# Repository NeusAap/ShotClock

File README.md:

# ShotClock hardware & software
This project entails the creation of a poker shot clock. The device is designed to manage the timing of player decisions during a poker game, enhancing the pace of play and ensuring fair timing for all participants. 

# Folder structure
1. `doc`: Contains design documents & notes/questions
2. `hw/ShotClockProject`: Contains KiCAD 7.0.6 design files for hardware
3. `hw/ShotClockProject/output`: Contains hardware output files (plots, PDFs etc.)
4. `sw`: contains STM32CubeIDE firmware

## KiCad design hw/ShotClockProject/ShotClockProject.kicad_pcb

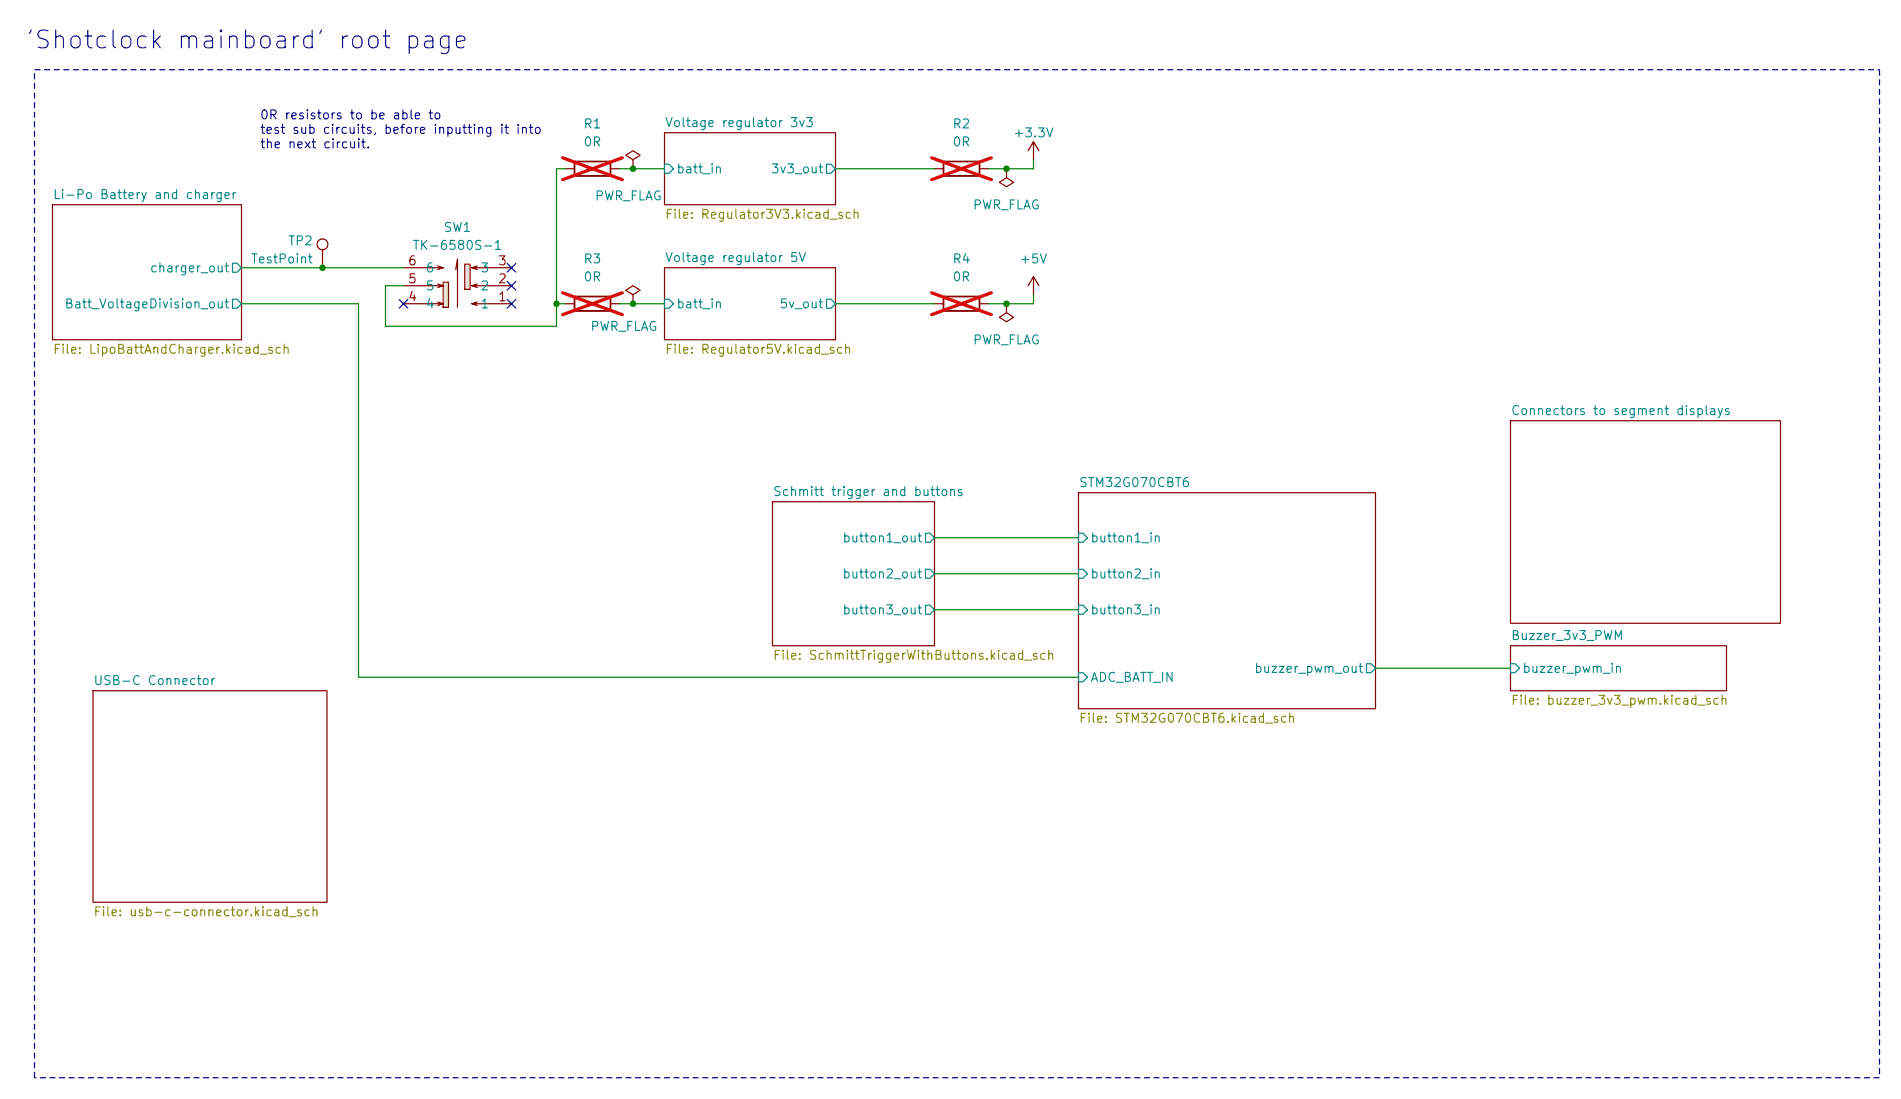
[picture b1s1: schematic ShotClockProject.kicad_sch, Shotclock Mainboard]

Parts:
R1, R2, R3, R4: 0R; R_0402_1005Metric; LCSC Part C17168; not fitted
SW1: TK-6580S-1; SW-SMD_TK-6580S-1; LCSC Part C528774
TP2: TestPoint; TestPoint_Pad_D1.0mm

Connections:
+3.3V: R2.2; also elsewhere on the board
+5V: R4.2; also elsewhere on the board
/Li-Po Battery and charger/charger_out: SW1.6, TP2.1; also elsewhere on the board
/Voltage regulator 3v3/3v3_out: R2.1; also elsewhere on the board
/Voltage regulator 3v3/batt_in: R1.2; also elsewhere on the board
/Voltage regulator 5V/5v_out: R4.1; also elsewhere on the board
/Voltage regulator 5V/batt_in: R3.2; also elsewhere on the board
unnamed: R1.1, R3.1, SW1.5

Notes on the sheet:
0R resistors to be able to test sub circuits, before inputting it into the next circuit.
'Shotclock mainboard' root page

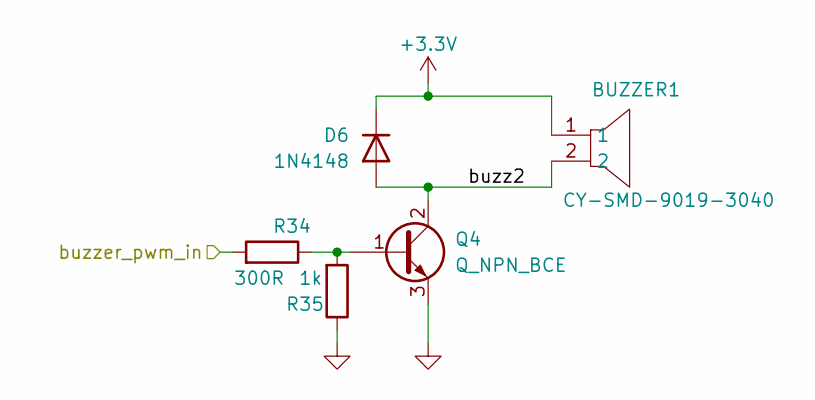
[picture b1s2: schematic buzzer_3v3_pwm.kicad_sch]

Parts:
BUZZER1: CY-SMD-9019-3040; BUZ-SMD_L9.0-W9.0-P8.00-LS9.3_CY; JLC Part Extended Part
D6: 1N4148; D_SOD-323; LCSC Part C2128
Q4: Q_NPN_BCE; SOT-23; LCSC Part C111113
R34: 300R; R_0402_1005Metric; LCSC Part C25102
R35: 1k; R_0402_1005Metric; LCSC Part C105637

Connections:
+3.3V: BUZZER1.1, D6.1 (K); also elsewhere on the board
/Buzzer_3v3_PWM/buzz2: BUZZER1.2, D6.2 (A), Q4.2 (C)
/Buzzer_3v3_PWM/buzzer_pwm_in: R34.2; also elsewhere on the board
GND: Q4.3 (E), R35.1; also elsewhere on the board
unnamed: Q4.1 (B), R34.1, R35.2

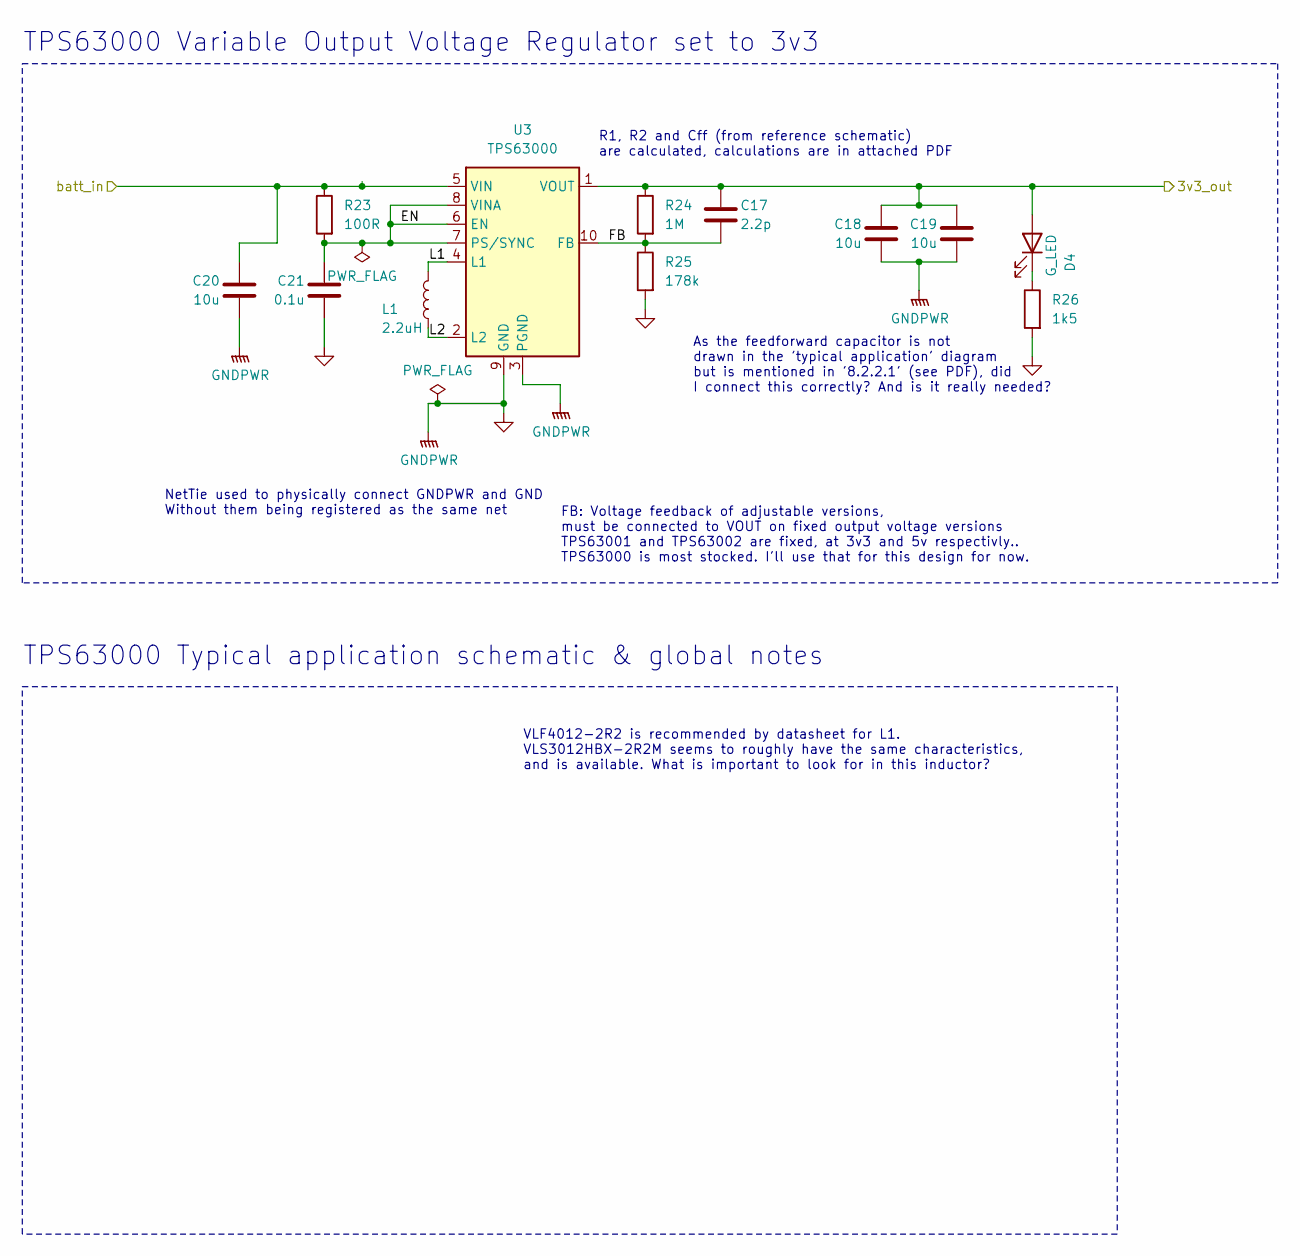
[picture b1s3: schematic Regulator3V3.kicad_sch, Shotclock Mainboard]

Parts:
C17: 2.2p; C_0402_1005Metric; LCSC Part C1559
C18, C19, C20: 10u; C_0603_1608Metric; LCSC Part C96446
C21: 0.1u; C_0402_1005Metric; LCSC Part C1525
D4: G_LED; LED_0603_1608Metric; LCSC Part C72043
L1: 2.2uH; L_Sunlord_SWPA3012S; LCSC Part C404494
R23: 100R; R_0402_1005Metric; LCSC Part C25076
R24: 1M; R_0402_1005Metric; LCSC Part C144787
R25: 178k; R_0402_1005Metric; LCSC Part C185459
R26: 1k5; R_0402_1005Metric; LCSC Part C25867
U3: TPS63000; Texas_DRC0010J_Altered; LCSC Part C24966

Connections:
/Voltage regulator 3v3/3v3_out: C17.1, C18.1, C19.1, D4.2 (A), R24.1, U3.1 (VOUT); also elsewhere on the board
/Voltage regulator 3v3/EN: C21.1, R23.2, U3.6 (EN), U3.7 (PS/SYNC), U3.8 (VINA)
/Voltage regulator 3v3/FB: C17.2, R24.2, R25.1, U3.10 (FB)
/Voltage regulator 3v3/L1: L1.1, U3.4 (L1)
/Voltage regulator 3v3/L2: L1.2, U3.2 (L2)
/Voltage regulator 3v3/batt_in: C20.1, R23.1, U3.5 (VIN); also elsewhere on the board
GND: C18.2, C19.2, C20.2, C21.2, R25.2, R26.2, U3.3 (PGND), U3.9 (GND), U3.11 (PGND); also elsewhere on the board
unnamed: D4.1 (K), R26.1

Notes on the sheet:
As the feedforward capacitor is not drawn in the 'typical application' diagram but is mentioned in '8.2.2.1' (see PDF), did I connect this correctly? And is it really needed?
NetTie used to physically connect GNDPWR and GND Without them being registered as the same net
R1, R2 and Cff (from reference schematic) are calculated, calculations are in attached PDF
FB: Voltage feedback of adjustable versions, must be connected to VOUT on fixed output voltage versions TPS63001 and TPS63002 are fixed, at 3v3 and 5v respectivly.. TPS63000 is most stocked. I'll use that for this design for now.
TPS63000 Variable Output Voltage Regulator set to 3v3
VLF4012-2R2 is recommended by datasheet for L1. VLS3012HBX-2R2M seems to roughly have the same characteristics, and is available. What is important to look for in this inductor?
TPS63000 Typical application schematic & global notes

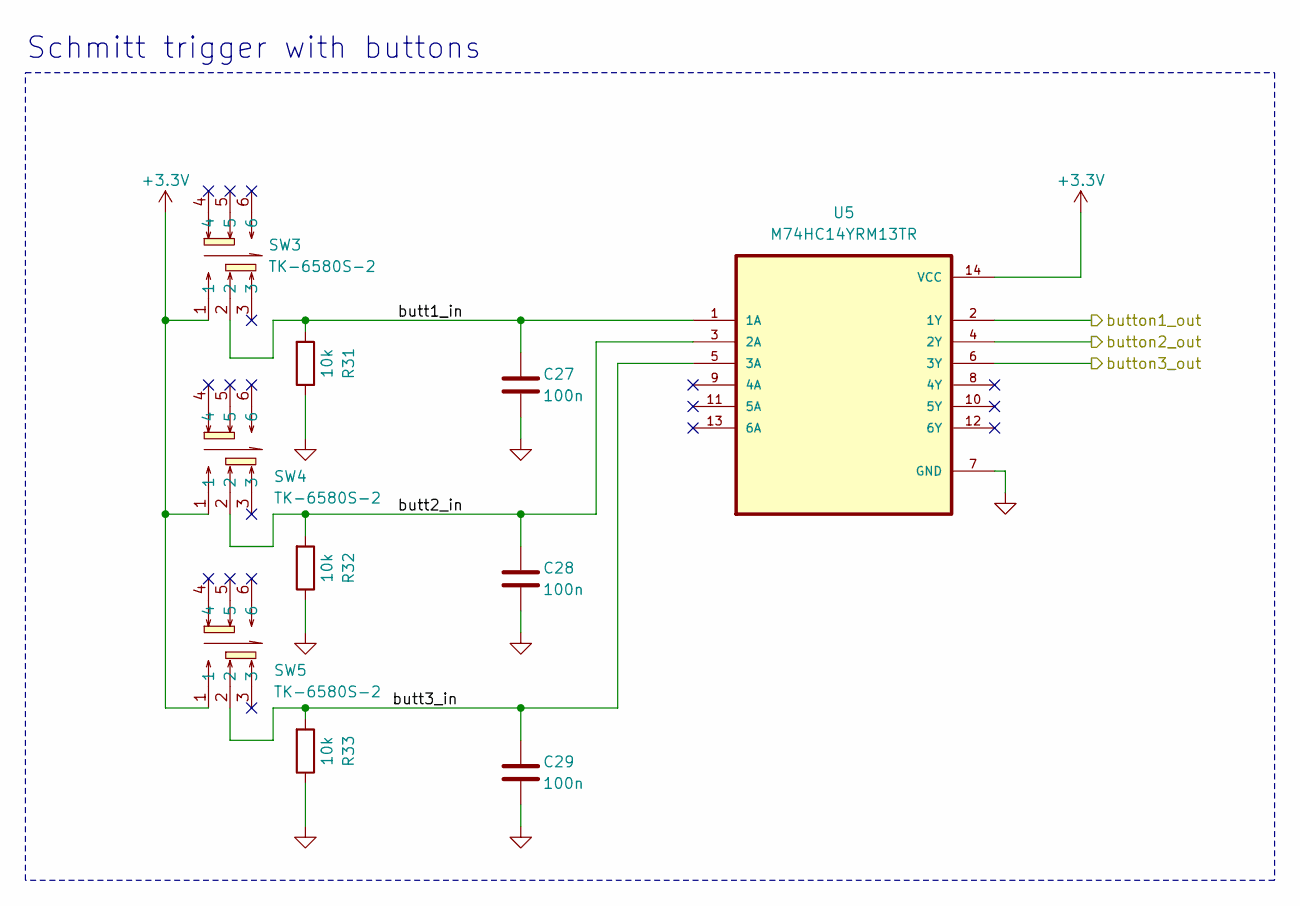
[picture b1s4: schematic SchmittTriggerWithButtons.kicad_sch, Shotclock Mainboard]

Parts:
C27, C28, C29: 100n; C_0402_1005Metric; LCSC Part C1525
R31, R32, R33: 10k; R_0402_1005Metric; LCSC Part C25744
SW3, SW4, SW5: TK-6580S-2; SW-SMD_TK-6580S-2; LCSC Part C528775
U5: M74HC14YRM13TR; SOIC-14_3.9x8.7mm_P1.27mm; LCSC Part C157450

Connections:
+3.3V: SW3.1, SW4.1, SW5.1, U5.14 (VCC); also elsewhere on the board
/STM32G070CBT6/button1_in: U5.2 (1Y); also elsewhere on the board
/STM32G070CBT6/button2_in: U5.4 (2Y); also elsewhere on the board
/STM32G070CBT6/button3_in: U5.6 (3Y); also elsewhere on the board
/Schmitt trigger and buttons/butt1_in: C27.1, R31.2, SW3.2, U5.1 (1A)
/Schmitt trigger and buttons/butt2_in: C28.1, R32.2, SW4.2, U5.3 (2A)
/Schmitt trigger and buttons/butt3_in: C29.1, R33.2, SW5.2, U5.5 (3A)
GND: C27.2, C28.2, C29.2, R31.1, R32.1, R33.1, U5.7 (GND); also elsewhere on the board

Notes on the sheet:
Schmitt trigger with buttons

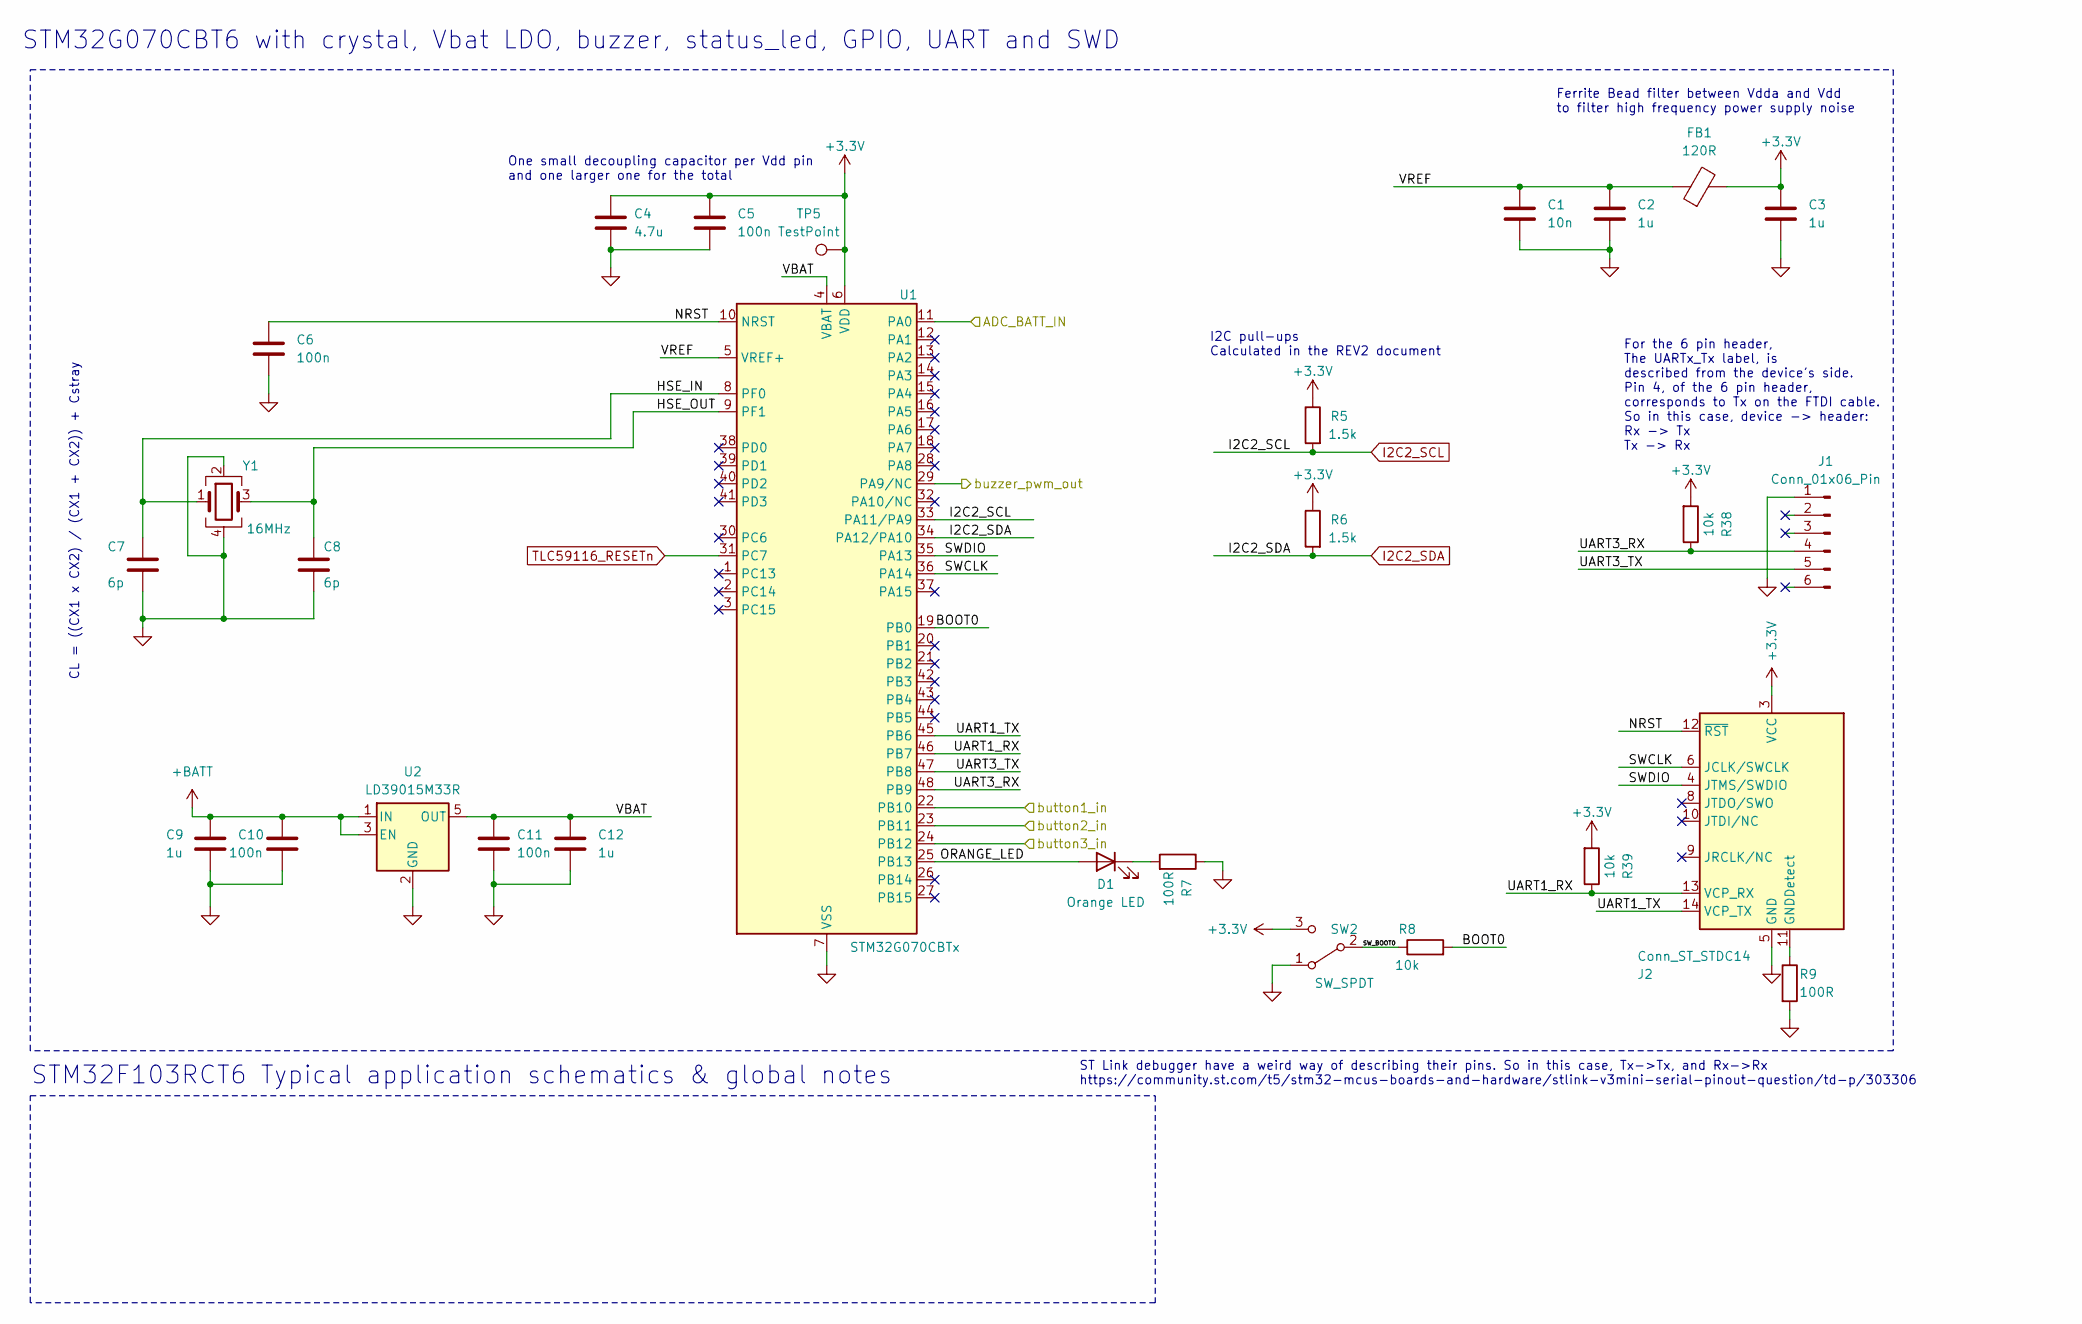
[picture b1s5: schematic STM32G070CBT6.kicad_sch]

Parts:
C1: 10n; C_0402_1005Metric; LCSC Part C15195
C2, C3, C9, C12: 1u; C_0402_1005Metric; LCSC Part C52923
C4: 4.7u; C_0402_1005Metric; LCSC Part C23733
C5, C6, C10, C11: 100n; C_0402_1005Metric; LCSC Part C1525
C7, C8: 6p; C_0402_1005Metric; LCSC Part C1575
D1: Orange LED; LED_0603_1608Metric; LCSC Part C264451
FB1: 120R; L_0603_1608Metric; LCSC Part C127301
J1: Conn_01x06_Pin; PinHeader_1x06_P2.54mm_Horizontal; LCSC Part C56816
J2: Conn_ST_STDC14; PinHeader_2x07_P1.27mm_Vertical_SMD; LCSC Part C3975190
R5, R6: 1.5k; R_0402_1005Metric; LCSC Part C25867
R7, R9: 100R; R_0402_1005Metric; LCSC Part C25076
R8, R38, R39: 10k; R_0402_1005Metric; LCSC Part C25744
SW2: SW_SPDT; SW_SPDT_PCM12_Upwards; LCSC Part C500057
TP5: TestPoint; TestPoint_Pad_D1.0mm
U1: STM32G070CBTx; LQFP-48_7x7mm_P0.5mm; LCSC Part C529338
U2: LD39015M33R; SOT-23-5; LCSC Part C2798212
Y1: 16MHz; Crystal_SMD_3225-4Pin_3.2x2.5mm; LCSC Part C112972

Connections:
+3.3V: C3.1, C4.1, C5.1, FB1.2, J2.3 (VCC), R5.1, R6.1, R38.2, R39.2, SW2.3 (C), TP5.1, U1.6 (VDD); also elsewhere on the board
+BATT: C9.1, C10.1, U2.1 (IN), U2.3 (EN); also elsewhere on the board
/Buzzer_3v3_PWM/buzzer_pwm_in: U1.29 (PA9/NC); also elsewhere on the board
/Li-Po Battery and charger/Batt_VoltageDivision_out: U1.11 (PA0); also elsewhere on the board
/STM32G070CBT6/BOOT0: R8.2, U1.19 (PB0)
/STM32G070CBT6/HSE_IN: C7.1, U1.8 (PF0), Y1.1
/STM32G070CBT6/HSE_OUT: C8.1, U1.9 (PF1), Y1.3
/STM32G070CBT6/NRST: C6.1, J2.12 (~RST), U1.10 (NRST)
/STM32G070CBT6/ORANGE_LED: D1.2 (A), U1.25 (PB13)
/STM32G070CBT6/SWCLK: J2.6 (JCLK/SWCLK), U1.36 (PA14)
/STM32G070CBT6/SWDIO: J2.4 (JTMS/SWDIO), U1.35 (PA13)
/STM32G070CBT6/SW_BOOT0: R8.1, SW2.2 (B)
/STM32G070CBT6/UART1_RX: J2.13 (VCP_RX), R39.1, U1.46 (PB7)
/STM32G070CBT6/UART1_TX: J2.14 (VCP_TX), U1.45 (PB6)
/STM32G070CBT6/UART3_RX: J1.4, R38.1, U1.48 (PB9)
/STM32G070CBT6/UART3_TX: J1.5, U1.47 (PB8)
/STM32G070CBT6/VBAT: C11.1, C12.1, U1.4 (VBAT), U2.5 (OUT)
/STM32G070CBT6/VREF: C1.1, C2.1, FB1.1, U1.5 (VREF+)
/STM32G070CBT6/button1_in: U1.22 (PB10); also elsewhere on the board
/STM32G070CBT6/button2_in: U1.23 (PB11); also elsewhere on the board
/STM32G070CBT6/button3_in: U1.24 (PB12); also elsewhere on the board
GND: C1.2, C2.2, C3.2, C4.2, C5.2, C6.2, C7.2, C8.2, C9.2, C10.2, C11.2, C12.2, J1.1, J2.5 (GND), J2.7 (GND), R7.1, R9.2, SW2.1 (A), U1.7 (VSS), U2.2 (GND), Y1.2, Y1.4; also elsewhere on the board
I2C2_SCL: R5.2, U1.33 (PA11/PA9); also elsewhere on the board
I2C2_SDA: R6.2, U1.34 (PA12/PA10); also elsewhere on the board
unnamed: D1.1 (K), R7.2
unnamed: J2.11 (GNDDetect), R9.1
TLC59116_RESETn: U1.31 (PC7); also elsewhere on the board

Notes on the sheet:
STM32F103RCT6 Typical application schematics & global notes
ST Link debugger have a weird way of describing their pins. So in this case, Tx->Tx, and Rx->Rx https://community.st.com/t5/stm32-mcus-boards-and-hardware/stlink-v3mini-serial-pinout-question/td-p/303306
For the 6 pin header, The UARTx_Tx label, is described from the device's side. Pin 4, of the 6 pin header, corresponds to Tx on the FTDI cable. So in this case, device -> header: Rx -> Tx Tx -> Rx
One small decoupling capacitor per Vdd pin and one larger one for the total
Ferrite Bead filter between Vdda and Vdd to filter high frequency power supply noise
I2C pull-ups Calculated in the REV2 document
STM32G070CBT6 with crystal, Vbat LDO, buzzer, status_led, GPIO, UART and SWD
CL = ((CX1 x CX2) / (CX1 + CX2)) + Cstray

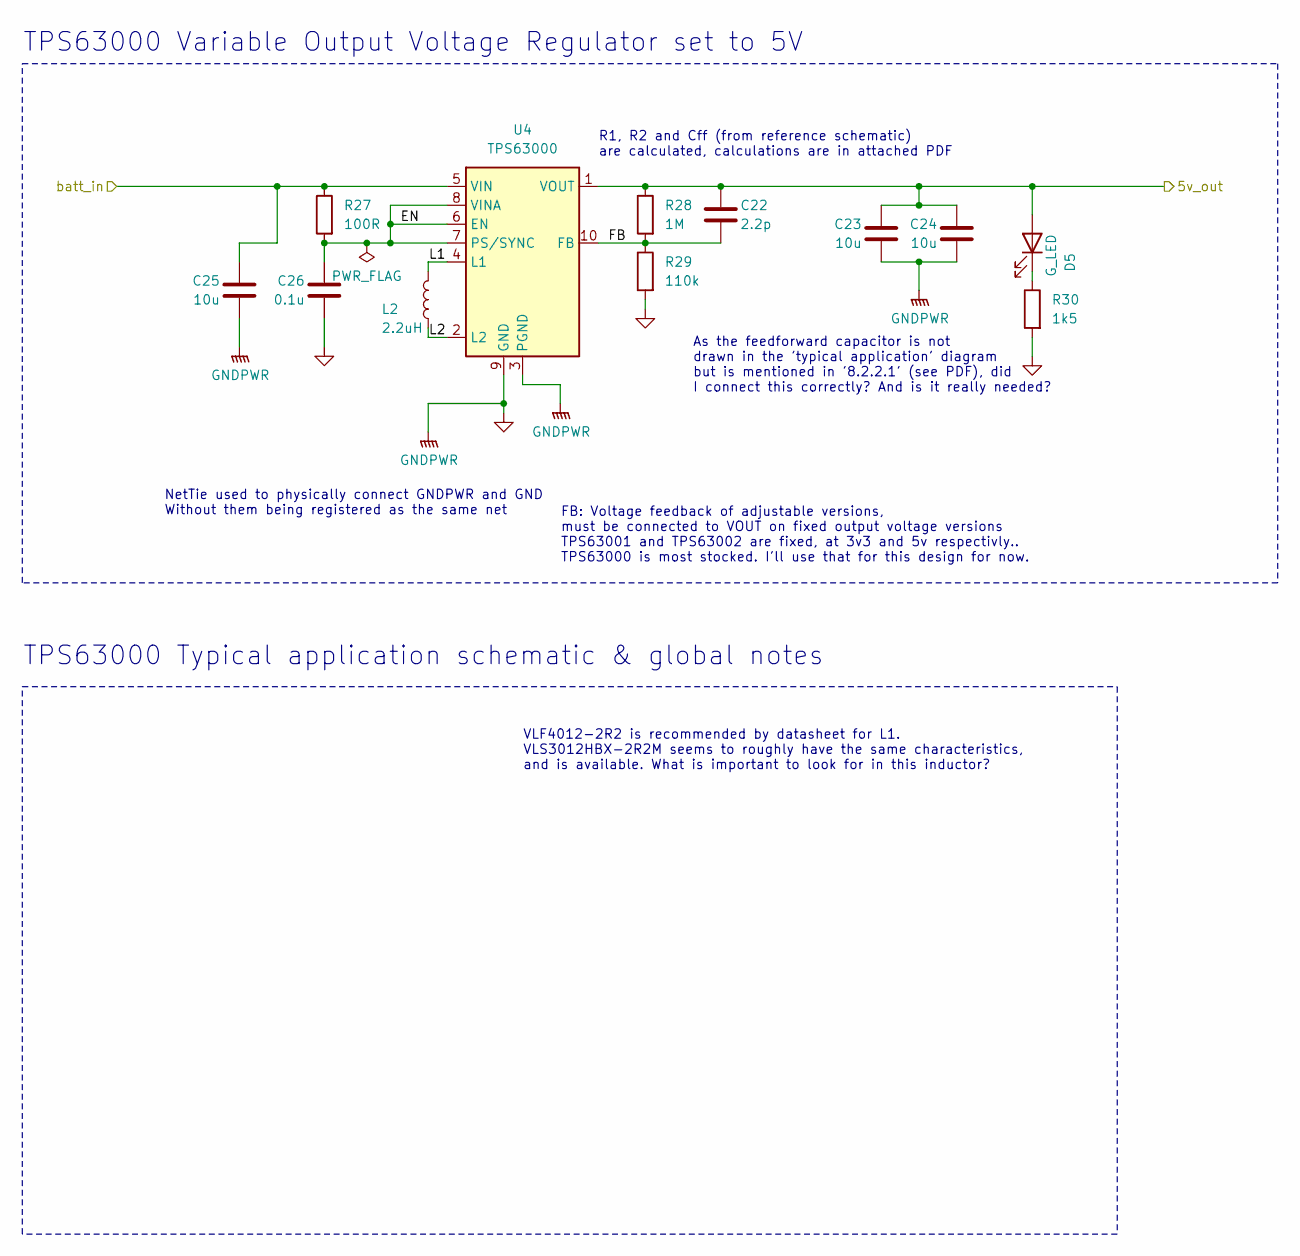
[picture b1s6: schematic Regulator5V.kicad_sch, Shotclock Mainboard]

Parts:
C22: 2.2p; C_0402_1005Metric; LCSC Part C1559
C23, C24, C25: 10u; C_0603_1608Metric; LCSC Part C96446
C26: 0.1u; C_0402_1005Metric; LCSC Part C1525
D5: G_LED; LED_0603_1608Metric; LCSC Part C72043
L2: 2.2uH; L_Sunlord_SWPA3012S; LCSC Part C404494
R27: 100R; R_0402_1005Metric; LCSC Part C25076
R28: 1M; R_0402_1005Metric; LCSC Part C144787
R29: 110k; R_0402_1005Metric; LCSC Part C25745
R30: 1k5; R_0402_1005Metric; LCSC Part C25867
U4: TPS63000; Texas_DRC0010J_Altered; LCSC Part C24966

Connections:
/Voltage regulator 5V/5v_out: C22.1, C23.1, C24.1, D5.2 (A), R28.1, U4.1 (VOUT); also elsewhere on the board
/Voltage regulator 5V/EN: C26.1, R27.2, U4.6 (EN), U4.7 (PS/SYNC), U4.8 (VINA)
/Voltage regulator 5V/FB: C22.2, R28.2, R29.1, U4.10 (FB)
/Voltage regulator 5V/L1: L2.1, U4.4 (L1)
/Voltage regulator 5V/L2: L2.2, U4.2 (L2)
/Voltage regulator 5V/batt_in: C25.1, R27.1, U4.5 (VIN); also elsewhere on the board
GND: C23.2, C24.2, C25.2, C26.2, R29.2, R30.2, U4.3 (PGND), U4.9 (GND), U4.11 (PGND); also elsewhere on the board
unnamed: D5.1 (K), R30.1

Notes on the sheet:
As the feedforward capacitor is not drawn in the 'typical application' diagram but is mentioned in '8.2.2.1' (see PDF), did I connect this correctly? And is it really needed?
NetTie used to physically connect GNDPWR and GND Without them being registered as the same net
R1, R2 and Cff (from reference schematic) are calculated, calculations are in attached PDF
FB: Voltage feedback of adjustable versions, must be connected to VOUT on fixed output voltage versions TPS63001 and TPS63002 are fixed, at 3v3 and 5v respectivly.. TPS63000 is most stocked. I'll use that for this design for now.
TPS63000 Variable Output Voltage Regulator set to 5V
VLF4012-2R2 is recommended by datasheet for L1. VLS3012HBX-2R2M seems to roughly have the same characteristics, and is available. What is important to look for in this inductor?
TPS63000 Typical application schematic & global notes

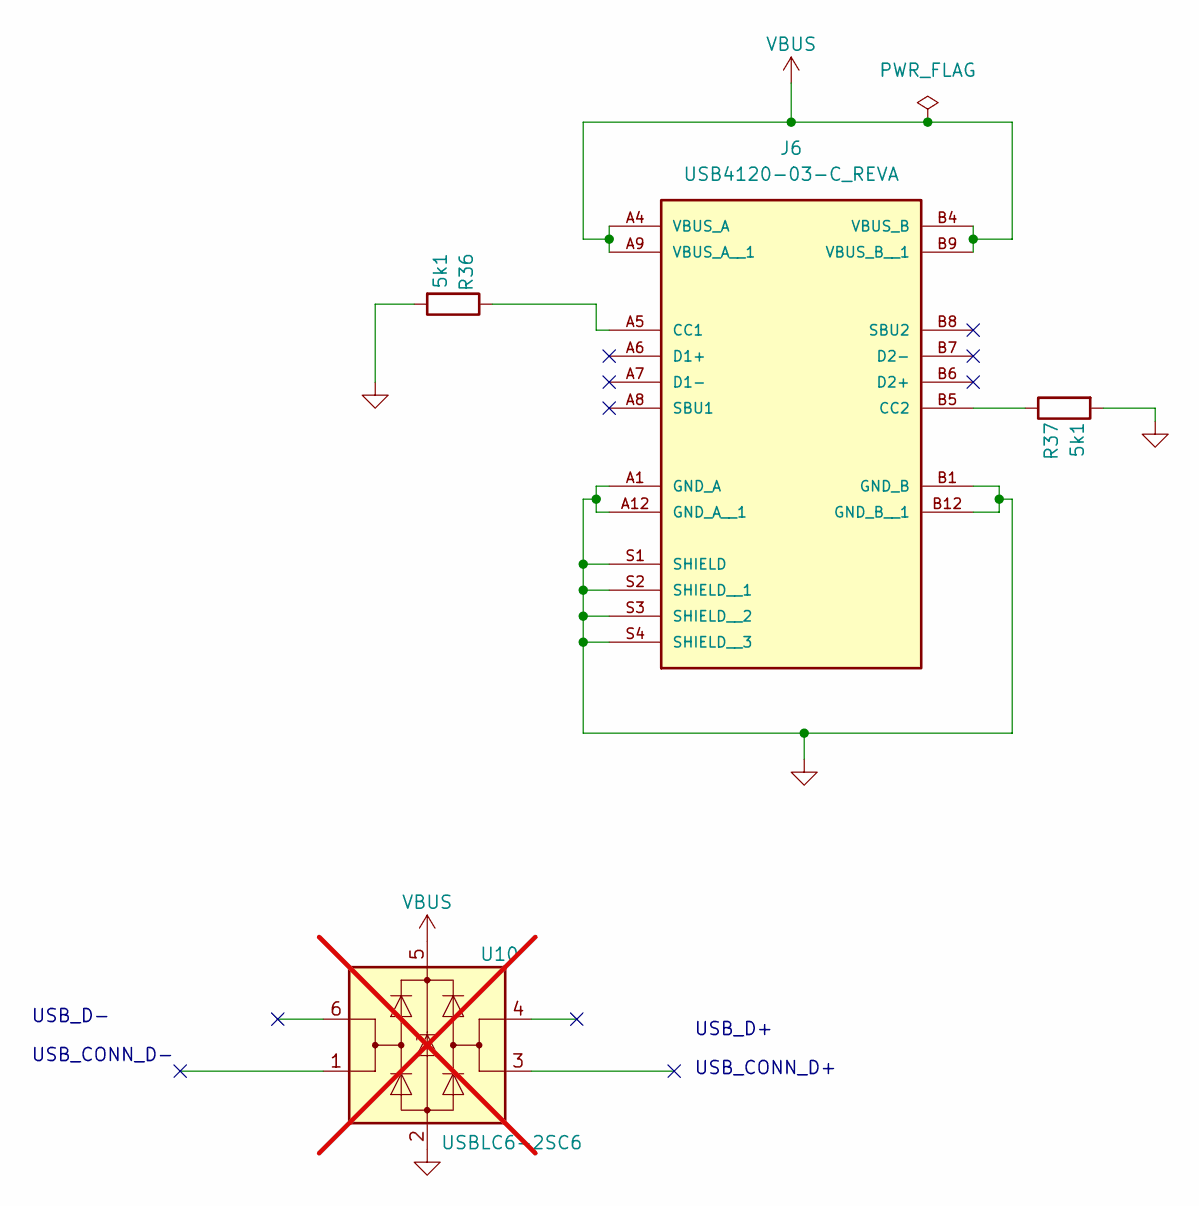
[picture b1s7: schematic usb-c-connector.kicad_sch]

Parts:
J6: USB4120-03-C_REVA; GCT_USB4120-03-C_REVA_With3DModel; PARTREV A; LCSC Part C5187468
R36, R37: 5k1; R_0402_1005Metric; LCSC Part C25905
U10: USBLC6-2SC6; SOT-23-6; LCSC Part C7519; not fitted

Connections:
GND: J6.A1 (GND_A), J6.A12 (GND_A__1), J6.B1 (GND_B), J6.B12 (GND_B__1), J6.S1 (SHIELD), J6.S2 (SHIELD__1), J6.S3 (SHIELD__2), J6.S4 (SHIELD__3), R36.2, R37.2, U10.2 (GND); also elsewhere on the board
unnamed: J6.A5 (CC1), R36.1
unnamed: J6.B5 (CC2), R37.1
VBUS: J6.A4 (VBUS_A), J6.A9 (VBUS_A__1), J6.B4 (VBUS_B), J6.B9 (VBUS_B__1), U10.5 (VBUS); also elsewhere on the board

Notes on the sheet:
USB_CONN_D-
USB_D-
USB_D+
USB_CONN_D+

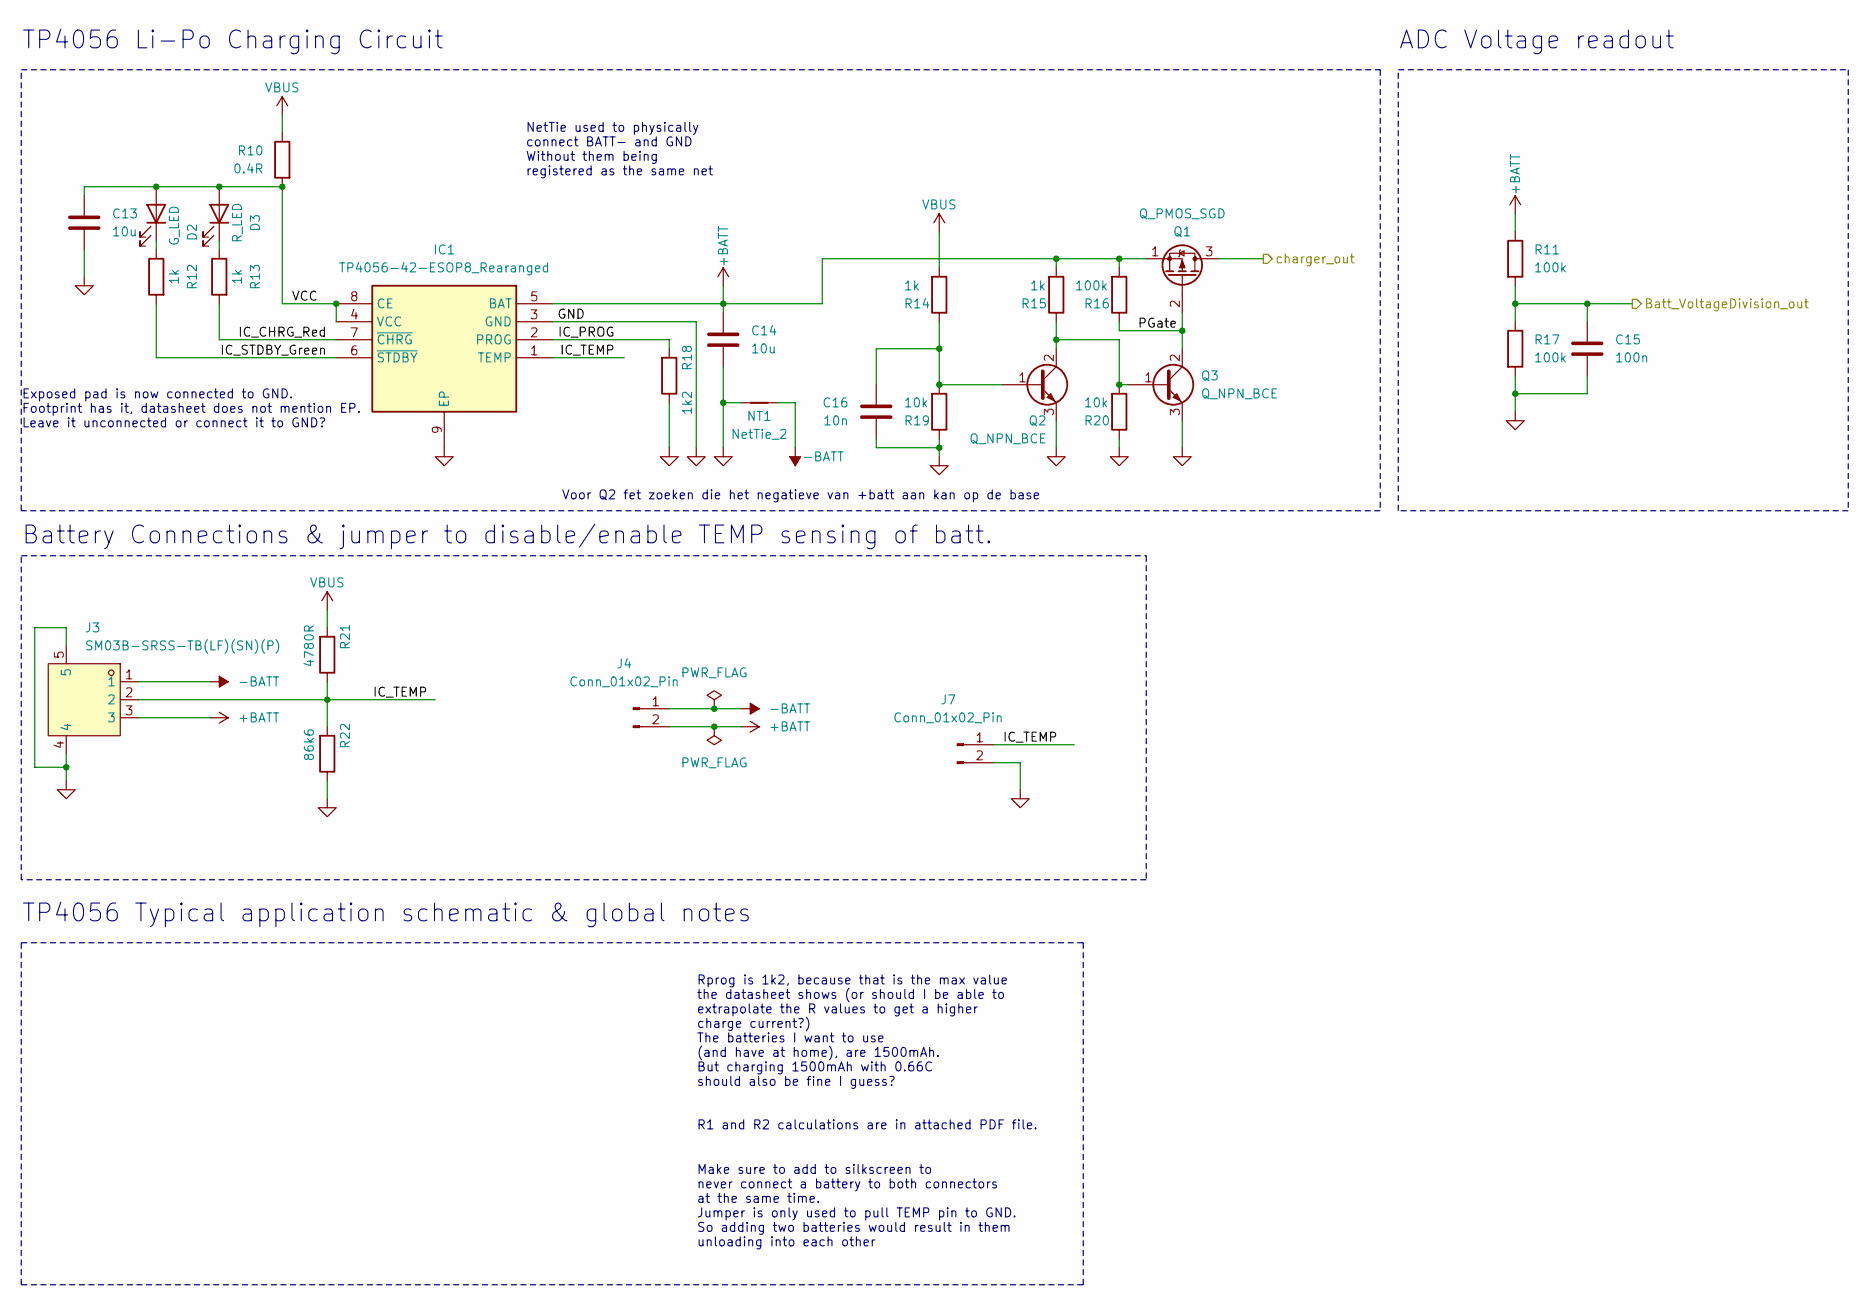
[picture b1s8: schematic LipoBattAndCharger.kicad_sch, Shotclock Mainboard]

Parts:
C13, C14: 10u; C_0402_1005Metric; LCSC Part C15525
C15: 100n; C_0402_1005Metric; LCSC Part C1525
C16: 10n; C_0402_1005Metric; LCSC Part C15195
D2: G_LED; LED_0603_1608Metric; LCSC Part C72043
D3: R_LED; LED_0603_1608Metric; LCSC Part C128250
IC1: TP4056-42-ESOP8_Rearanged; Texas_HSOP-8-1EP_3.9x4.9mm_P1.27mm; Manufacturer_Part_Number TP4056-42-ESOP8; LCSC Part C725790
J3: SM03B-SRSS-TB(LF)(SN)(P); CONN-SMD_SM03B-SRSS-TB-LF-SN-P; JLC Part Extended Part
J4, J7: Conn_01x02_Pin; PinHeader_1x02_P2.54mm_Horizontal; LCSC Part C492410
NT1: NetTie_2; NetTie-2_SMD_Pad0.5mm
Q1: Q_PMOS_SGD; TO-263-2; LCSC Part C33903
Q2, Q3: Q_NPN_BCE; SOT-23; LCSC Part C111113
R10: 0.4R; R_0402_1005Metric; LCSC Part C27147
R11, R16, R17: 100k; R_0402_1005Metric; LCSC Part C25741
R12, R13, R14, R15: 1k; R_0402_1005Metric; LCSC Part C105637
R18: 1k2; R_0402_1005Metric; LCSC Part C25862
R19, R20: 10k; R_0402_1005Metric; LCSC Part C25744
R21: 4780R; R_0402_1005Metric; LCSC Part C25900
R22: 86k6; R_0402_1005Metric; LCSC Part C852935

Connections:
+BATT: C14.1, IC1.5 (BAT), J3.3, J4.2, Q1.1 (S), R11.1, R15.2, R16.2; also elsewhere on the board
-BATT: J3.1, J4.1, NT1.2
/Li-Po Battery and charger/Batt_VoltageDivision_out: C15.1, R11.2, R17.1; also elsewhere on the board
/Li-Po Battery and charger/IC_CHRG_Red: IC1.7 (~CHRG), R13.2
/Li-Po Battery and charger/IC_PROG: IC1.2 (PROG), R18.2
/Li-Po Battery and charger/IC_STDBY_Green: IC1.6 (~STDBY), R12.2
/Li-Po Battery and charger/IC_TEMP: IC1.1 (TEMP), J3.2, J7.1, R21.1, R22.2
/Li-Po Battery and charger/PGate: Q1.2 (G), Q3.2 (C), R16.1
/Li-Po Battery and charger/VCC: C13.1, D2.2 (A), D3.2 (A), IC1.4 (VCC), IC1.8 (CE), R10.2
/Li-Po Battery and charger/charger_out: Q1.3 (D); also elsewhere on the board
GND: C13.2, C14.2, C15.2, C16.2, IC1.3 (GND), IC1.9 (EP), J3.4, J3.5, J7.2, NT1.1, Q2.3 (E), Q3.3 (E), R17.2, R18.1, R19.1, R20.1, R22.1; also elsewhere on the board
unnamed: D2.1 (K), R12.1
unnamed: D3.1 (K), R13.1
unnamed: C16.1, Q2.1 (B), R14.1, R19.2
unnamed: Q2.2 (C), Q3.1 (B), R15.1, R20.2
VBUS: R10.1, R14.2, R21.2; also elsewhere on the board

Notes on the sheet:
Rprog is 1k2, because that is the max value the datasheet shows (or should I be able to extrapolate the R values to get a higher charge current?) The batteries I want to use (and have at home), are 1500mAh. But charging 1500mAh with 0.66C should also be fine I guess? R1 and R2 calculations are in a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
TP4056 Li-Po Charging Circuit
TP4056 Typical application schematic & global notes
ADC Voltage readout
Battery Connections & jumper to disable/enable TEMP sensing of batt.
Make sure to add to silkscreen to never connect a battery to both connectors at the same time. Jumper is only used to pull TEMP pin to GND. So adding two batteries would result in them unloading into each other
Voor Q2 fet zoeken die het negatieve van +batt aan kan op de base
NetTie used to physically connect BATT- and GND Without them being registered as the same net
Exposed pad is now connected to GND. Footprint has it, datasheet does not mention EP. Leave it unconnected or connect it to GND?

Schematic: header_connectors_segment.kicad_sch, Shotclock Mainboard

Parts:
U6, U7, U8, U9: S6B-PH-K-S-(LF)(SN); CONN-TH_6P-P2.00_S6B-PH-K-S-LF-SN; LCSC Part C157920

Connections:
+3.3V: U6.2, U7.2, U8.2, U9.2; also elsewhere on the board
+5V: U6.3, U7.3, U8.3, U9.3; also elsewhere on the board
GND: U6.6, U7.6, U8.6, U9.6; also elsewhere on the board
I2C2_SCL: U6.4, U7.4, U8.4, U9.4; also elsewhere on the board
I2C2_SDA: U6.5, U7.5, U8.5, U9.5; also elsewhere on the board
TLC59116_RESETn: U6.1, U7.1, U8.1, U9.1; also elsewhere on the board

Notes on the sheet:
Connections to the seven (eight) segment display PCB's (4 connectors, each rotated 90° in the end product)
